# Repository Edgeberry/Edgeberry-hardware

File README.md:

The **Edgeberry Base Board** provides essential additional functionality for deploying the Raspberry Pi Model B as an IoT edge device in a real-world environment.

- **12 to 24VDC input power supply** for reliably powering the device with up to 3A at 5V.
- **Indicators and button** for providing status feedback and device interaction
- **Expansion slot** for Edgeberry Hardware Cartridges
- **Robust enclosure** for withstanding the environmental challenges of the real world
<br/>
<br clear="right"/>

## Edgeberry Device Software
For using your Edgeberry hardware with the Edgeberry ecosystem (e.g. the Edgeberry Dashboard), you'll need to install the [Edgeberry Device Software](https://github.com/Edgeberry/Edgeberry/). Follow [these installation steps](https://github.com/Edgeberry/Edgeberry?tab=readme-ov-file#installation). If you have different plans with this board, this software is not required for correct operation of any of its hardware components.

## (re)Writing the EEPROM
>[!important]
>**When you purchased the Edgeberry Hardware, the manufacturer has written the EEPROM**. If you are the manufacturer, or you're hacking your Edgeberry board, then continue with the following steps.

1) Close the `write protection` jumper (JP1) on the Edgeberry Hardware to enable writing the EEPROM
2) Download and build the [Raspberry Pi Hat eeprom utils](https://github.com/raspberrypi/hats) on your device 
3) Make the EEPROM file from the eeprom_settings.txt using `eepmake` <br> e.g. `$ ./eepmake eeprom_settings.txt edgeberry.eep`
4) Flash the EEPROM using `eepflash.sh` <br> e.g. `$ sudo ./eepflash -w -t=24c256 -f=edgeberry.eep`
5) Now `reboot` the device and check the device tree for your hat's settings <br> e.g. `$ cat /proc/device-tree/hat/vendor`)

## License & Collaboration
**Copyright© 2024 Sanne 'SpuQ' Santens**. This project is released under the [**CERN OHL-W**](./LICENSE.txt) license. The [Rules & Guidelines](https://github.com/Edgeberry/.github/blob/main/brand/Edgeberry_Trademark_Rules_and_Guidelines.md) apply to the usage of the Edgeberry™ brand.

### Collaboration

If you'd like to contribute to this project, please follow these guidelines:
1. Fork the repository and create your branch from `main`.
2. Make your changes and ensure they adhere to the project's design style and conventions.
3. Test your changes thoroughly.
4. Ensure your commits are descriptive and well-documented.
5. Open a pull request, describing the changes you've made and the problem or feature they address.

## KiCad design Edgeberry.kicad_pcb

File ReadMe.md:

# EDGEBERRY Hardware

The Raspberry Pi compatible 'hat' for the Edgeberry project.

## License and contribution
Copyright Sanne 'SpuQ' Santens. All rights reserved. For now.

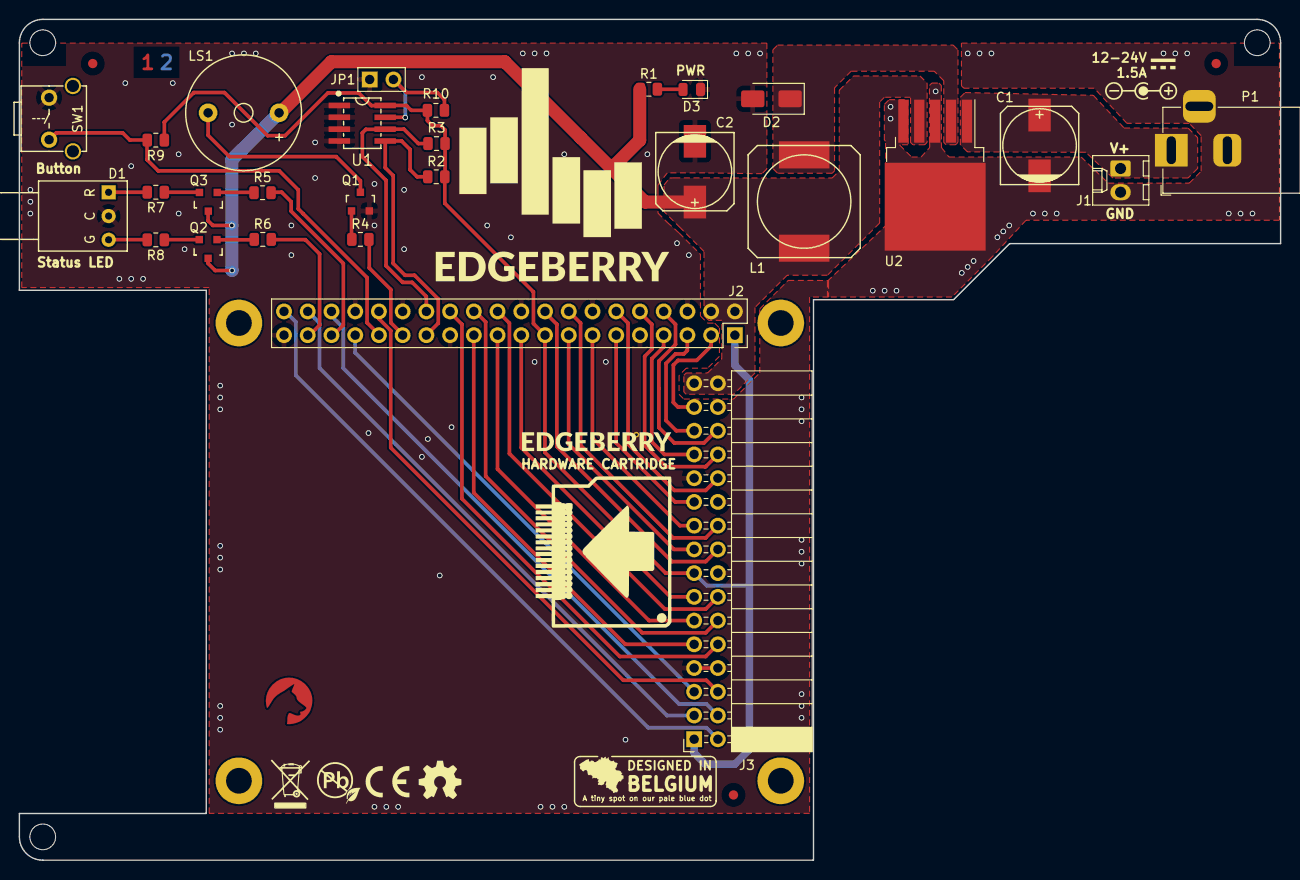
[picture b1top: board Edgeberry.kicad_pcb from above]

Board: 2 copper layers, 135.0 x 90.0 mm, 28 parts (0 on the bottom side), 43 nets.

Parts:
C1, C2: 330uF; c_elec_8x10
D1: Led_x2; bicolor_LED_right_angle
D2: SS54; D_SMA
D3: LED; LED_0805_2012Metric
J1: Molex_KK_1x02_P2.54mm; Molex_KK-254_AE-6410-02A_1x02_P2.54mm_Vertical
J2: Raspberry_Pi_2_3; PinSocket_2x20_P2.54mm_Vertical
J3: Edgeberry Cartridge Connector; PinSocket_2x16_P2.54mm_Horizontal
JP1: Jumper_2_Open; PinHeader_1x02_P2.54mm_Vertical
L1: 33uH; SELF-WE-PD-XXL
LS1: Buzzer; Buzzer_12x9.5RM7.6
P1: 12Vin; BarrelJack_Horizontal
Q1, Q2, Q3: BC547; SOT-23
R1, R7, R8: 270R; R_0805_2012Metric
R2, R3, R9, R10: 10k; R_0805_2012Metric
R4, R5, R6: 3k3; R_0805_2012Metric
SW1: SW_PUSH; tactile_switch_vertical
U1: 24LC256; SOIC_8
U2: LM2596S-5.0; TO-263-5_TabPin3

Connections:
+3V3: J2.1 (3V3), J2.17 (3V3), J3.1 (3V3_Power), J3.15 (3V3_Power), R2.1, R3.1, R9.1, R10.1, U1.8 (Vcc)
+5V: C2.1, J2.2 (5V), J2.4 (5V), J3.31 (5V_Power), J3.32 (5V_Power), L1.2, LS1.1, Q2.3 (C), Q3.3 (C), R1.1, U2.4 (FB)
+12V: C1.1, J1.1, P1.1, U2.1 (Vin)
GND: C1.2, C2.2, D1.2 (K), D2.2 (A), D3.1 (K), J1.2, J2.6 (GND), J2.9 (GND), J2.14 (GND), J2.20 (GND), J2.25 (GND), J2.30 (GND), J2.34 (GND), J2.39 (GND), J3.7 (GND), J3.8 (GND), J3.16 (GND), J3.22 (GND), J3.23 (GND), J3.30 (GND), JP1.1 (A), P1.2, P1.3, Q1.2 (E), SW1.1, U1.1 (A0), U1.2 (A1), U1.3 (A2), U1.4 (Vss), U2.3 (GND), U2.5 (on/off)
GPIO_4: J2.7 (GCLK0/GPIO4), J3.25 (GPIO_4)
GPIO_12: J2.32 (PWM0/GPIO12), J3.6 (GPIO_12)
GPIO_13: J2.33 (PWM1/GPIO13), J3.5 (GPIO_13)
GPIO_16: J2.36 (GPIO16), J3.4 (GPIO_16)
GPIO_17: J2.11 (GPIO17), J3.21 (GPIO_17)
GPIO_18: J2.12 (GPIO18/PWM0), J3.24 (GPIO_18)
GPIO_20: J2.38 (GPIO20/MOSI1), J3.3 (GPIO_20)
GPIO_21: J2.40 (GPIO21/SCLK1), J3.2 (GPIO_21)
GPIO_22: J2.15 (GPIO22), J3.17 (GPIO_22)
GPIO_23: J2.16 (GPIO23), J3.20 (GPIO_23)
GPIO_24: J2.18 (GPIO24), J3.18 (GPIO_24)
GPIO_25: J2.22 (GPIO25), J3.14 (GPIO_25)
GPIO_27: J2.13 (GPIO27), J3.19 (GPIO_27)
I2C_SCL: J2.5 (SCL/GPIO3), J3.27 (I2C_SCL)
I2C_SDA: J2.3 (SDA/GPIO2), J3.29 (I2C_SDA)
ID_SCL: J2.28 (ID_SC/GPIO1), R3.2, U1.6 (SCL)
ID_SDA: J2.27 (ID_SD/GPIO0), R2.2, U1.5 (SDA)
LED_green: J2.37 (GPIO26), R6.2
LED_red: J2.35 (GPIO19/MISO1), R5.2
unnamed: D1.1 (A1), R7.2
unnamed: D1.3 (A2), R8.2
unnamed: D2.1 (K), L1.1, U2.2 (Vout)
unnamed: D3.2 (A), R1.2
unnamed: Q1.1 (B), R4.1
unnamed: LS1.2, Q1.3 (C)
unnamed: Q2.1 (B), R6.1
unnamed: Q2.2 (E), R8.1
unnamed: Q3.1 (B), R5.1
unnamed: Q3.2 (E), R7.1
SPI_CS0: J2.24 (~CE0/GPIO8), J3.12 (SPI_CS0)
SPI_CS1: J2.26 (~CE1/GPIO7), J3.10 (SPI_CS1)
SPI_MISO: J2.21 (MISO0/GPIO9), J3.11 (SPI_MISO)
SPI_MOSI: J2.19 (MOSI0/GPIO10), J3.13 (SPI_MOSI)
SPI_SCLK: J2.23 (SCLK0/GPIO11), J3.9 (SPI_SCLK)
UART_RX: J2.10 (GPIO15/RXD), J3.26 (UART_Rx)
UART_TX: J2.8 (GPIO14/TXD), J3.28 (UART_Tx)
WP: JP1.2 (B), R10.2, U1.7 (WP)
btn_1: J2.31 (GCLK2/GPIO6), R9.2, SW1.2
buzzer: J2.29 (GCLK1/GPIO5), R4.2

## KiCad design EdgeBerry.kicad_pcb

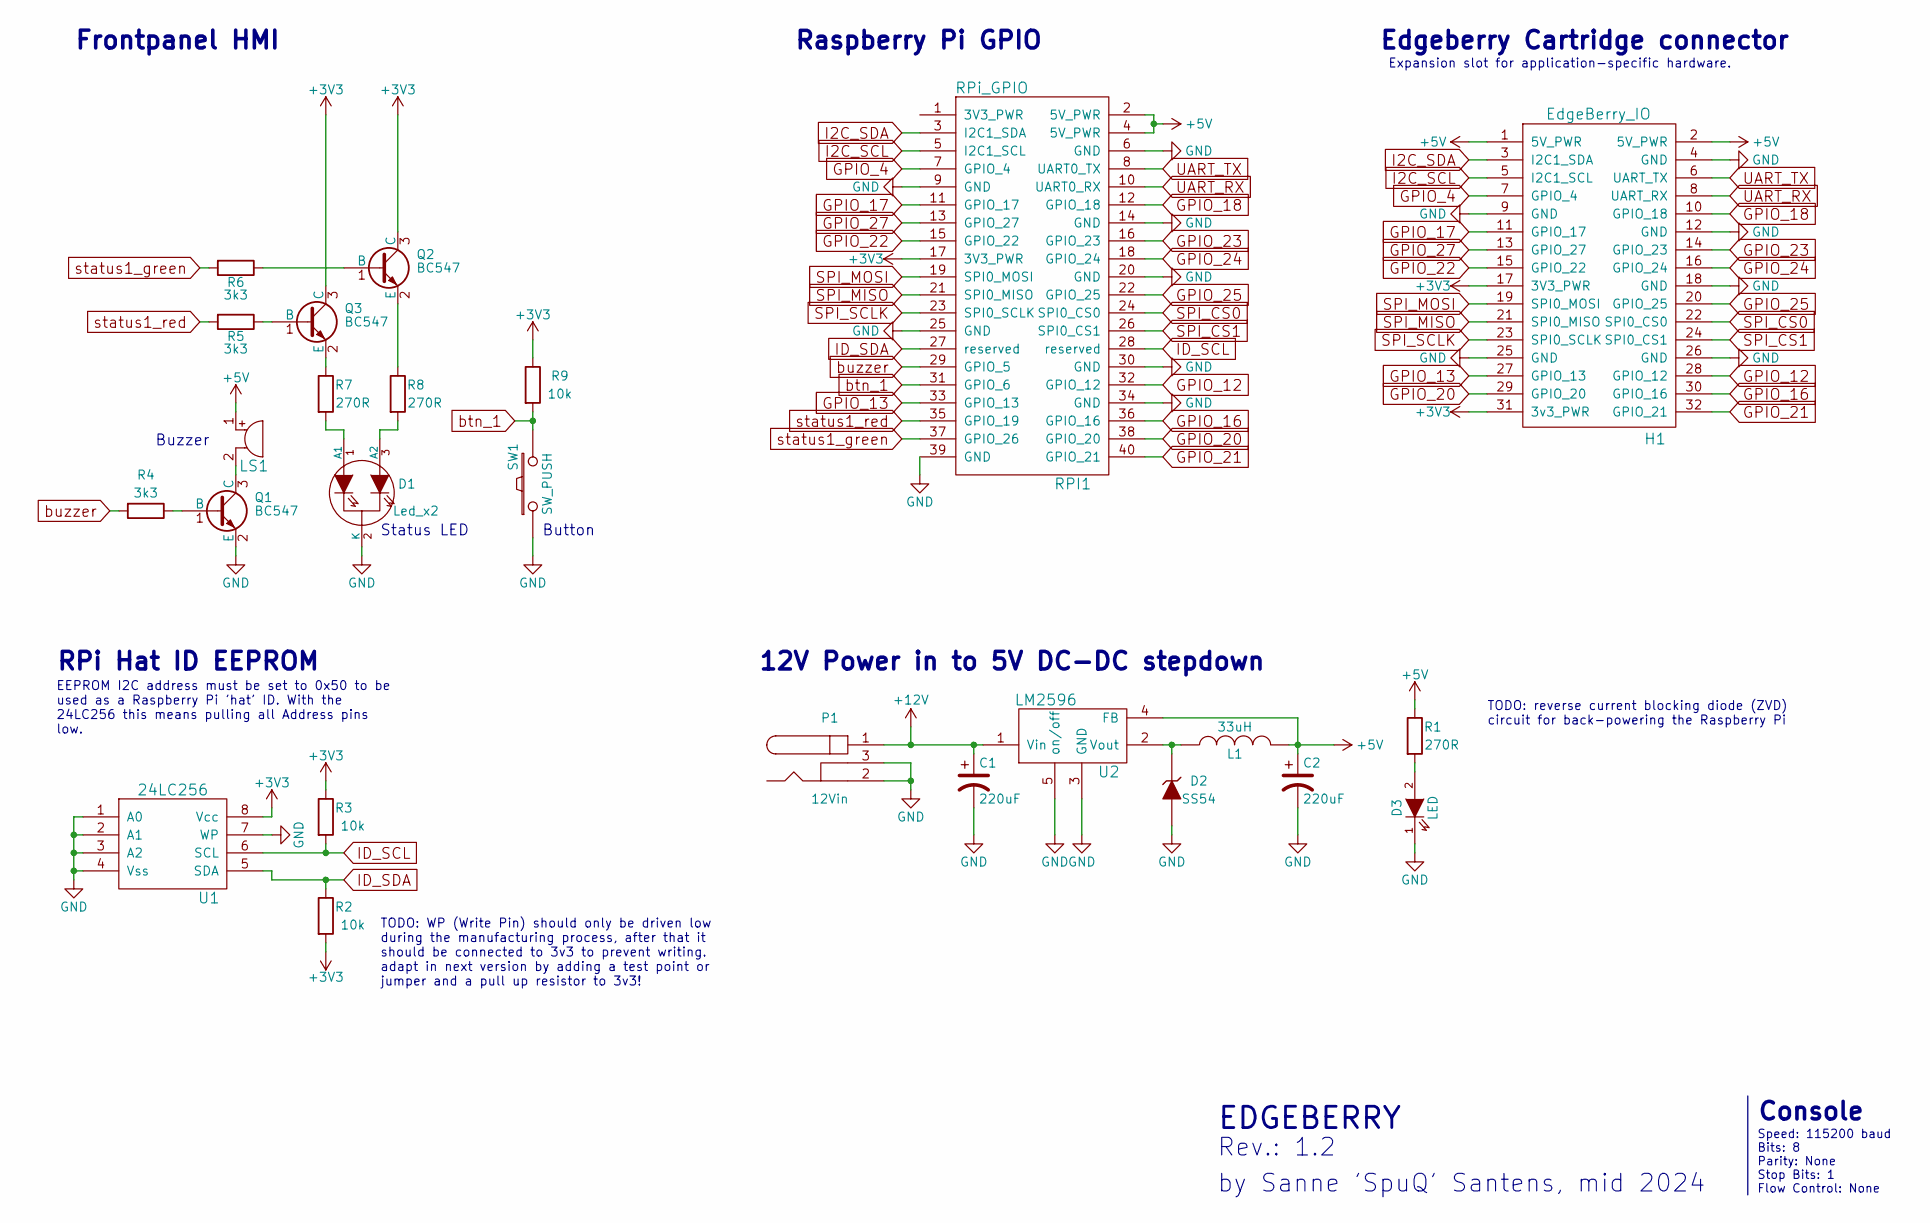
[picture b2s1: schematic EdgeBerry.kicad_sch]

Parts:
C1, C2: 220uF; c_elec_8x10
D1: Led_x2; bicolor_LED_right_angle
D2: SS54; SS54_Schottky_40V_5A
D3: LED; LED_0805_2012Metric
H1: EdgeBerry_IO
L1: 33uH; SELF-WE-PD-XXL
LS1: Buzzer; Buzzer_12x9.5RM7.6
P1: 12Vin; BarrelJack_Horizontal
Q1, Q2, Q3: BC547; SOT-23
R1, R7, R8: 270R; R_0805_2012Metric
R2, R3, R9: 10k; R_0805_2012Metric
R4, R5, R6: 3k3; R_0805_2012Metric
RPI1: RPi_GPIO; RPI_GPIO
SW1: SW_PUSH; tactile_switch_vertical
U1: 24LC256; SOIC_8
U2: LM2596; TO-263-5_TabPin3

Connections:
+3V3: H1.17 (3V3_PWR), H1.31 (3v3_PWR), Q2.3 (C), Q3.3 (C), R2.2, R3.1, R9.1, RPI1.17 (3V3_PWR), U1.8 (Vcc)
+5V: C2.1, H1.1 (5V_PWR), H1.2 (5V_PWR), L1.2, LS1.1, R1.1, RPI1.2 (5V_PWR), RPI1.4 (5V_PWR), U2.4 (FB)
+12V: C1.1, P1.1, U2.1 (Vin)
GND: C1.2, C2.2, D1.2 (K), D2.2 (A), D3.1 (K), H1.4 (GND), H1.9 (GND), H1.12 (GND), H1.18 (GND), H1.25 (GND), H1.26 (GND), P1.2, P1.3, Q1.2 (E), RPI1.6 (GND), RPI1.9 (GND), RPI1.14 (GND), RPI1.20 (GND), RPI1.25 (GND), RPI1.30 (GND), RPI1.34 (GND), RPI1.39 (GND), SW1.1, U1.1 (A0), U1.2 (A1), U1.3 (A2), U1.4 (Vss), U1.7 (WP), U2.3 (GND), U2.5 (on/off)
GPIO_4: H1.7 (GPIO_4), RPI1.7 (GPIO_4)
GPIO_12: H1.28 (GPIO_12), RPI1.32 (GPIO_12)
GPIO_13: H1.27 (GPIO_13), RPI1.33 (GPIO_13)
GPIO_16: H1.30 (GPIO_16), RPI1.36 (GPIO_16)
GPIO_17: H1.11 (GPIO_17), RPI1.11 (GPIO_17)
GPIO_18: H1.10 (GPIO_18), RPI1.12 (GPIO_18)
GPIO_20: H1.29 (GPIO_20), RPI1.38 (GPIO_20)
GPIO_21: H1.32 (GPIO_21), RPI1.40 (GPIO_21)
GPIO_22: H1.15 (GPIO_22), RPI1.15 (GPIO_22)
GPIO_23: H1.14 (GPIO_23), RPI1.16 (GPIO_23)
GPIO_24: H1.16 (GPIO_24), RPI1.18 (GPIO_24)
GPIO_25: H1.20 (GPIO_25), RPI1.22 (GPIO_25)
GPIO_27: H1.13 (GPIO_27), RPI1.13 (GPIO_27)
I2C_SCL: H1.5 (I2C1_SCL), RPI1.5 (I2C1_SCL)
I2C_SDA: H1.3 (I2C1_SDA), RPI1.3 (I2C1_SDA)
ID_SCL: R3.2, RPI1.28 (reserved), U1.6 (SCL)
ID_SDA: R2.1, RPI1.27 (reserved), U1.5 (SDA)
unnamed: D1.1 (A1), R7.2
unnamed: D1.3 (A2), R8.2
unnamed: D2.1 (K), L1.1, U2.2 (Vout)
unnamed: D3.2 (A), R1.2
unnamed: LS1.2, Q1.3 (C)
unnamed: Q1.1 (B), R4.1
unnamed: Q2.1 (B), R6.1
unnamed: Q2.2 (E), R8.1
unnamed: Q3.1 (B), R5.1
unnamed: Q3.2 (E), R7.1
SPI_CS0: H1.22 (SPI0_CS0), RPI1.24 (SPI0_CS0)
SPI_CS1: H1.24 (SPI0_CS1), RPI1.26 (SPI0_CS1)
SPI_MISO: H1.21 (SPI0_MISO), RPI1.21 (SPI0_MISO)
SPI_MOSI: H1.19 (SPI0_MOSI), RPI1.19 (SPI0_MOSI)
SPI_SCLK: H1.23 (SPI0_SCLK), RPI1.23 (SPI0_SCLK)
UART_RX: H1.8 (UART_RX), RPI1.10 (UART0_RX)
UART_TX: H1.6 (UART_TX), RPI1.8 (UART0_TX)
btn_1: R9.2, RPI1.31 (GPIO_6), SW1.2
buzzer: R4.2, RPI1.29 (GPIO_5)
status1_green: R6.2, RPI1.37 (GPIO_26)
status1_red: R5.2, RPI1.35 (GPIO_19)

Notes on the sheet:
Button
Speed: 115200 baud Bits: 8 Parity: None Stop Bits: 1 Flow Control: None
by Sanne 'SpuQ' Santens, mid 2024
EEPROM I2C address must be set to 0x50 to be used as a Raspberry Pi 'hat' ID. With the 24LC256 this means pulling all Address pins low.
Frontpanel HMI
12V Power in to 5V DC-DC stepdown
Raspberry Pi GPIO
TODO: reverse current blocking diode (ZVD) circuit for back-powering the Raspberry Pi
RPi Hat ID EEPROM
Console
Rev.: 1.2
Buzzer
Status LED
TODO: WP (Write Pin) should only be driven low during the manufacturing process, after that it should be connected to 3v3 to prevent writing. adapt in next version by adding a test point or jumper and a pull up resistor to 3v3!
EDGEBERRY
Expansion slot for application-specific hardware.
Edgeberry Cartridge connector

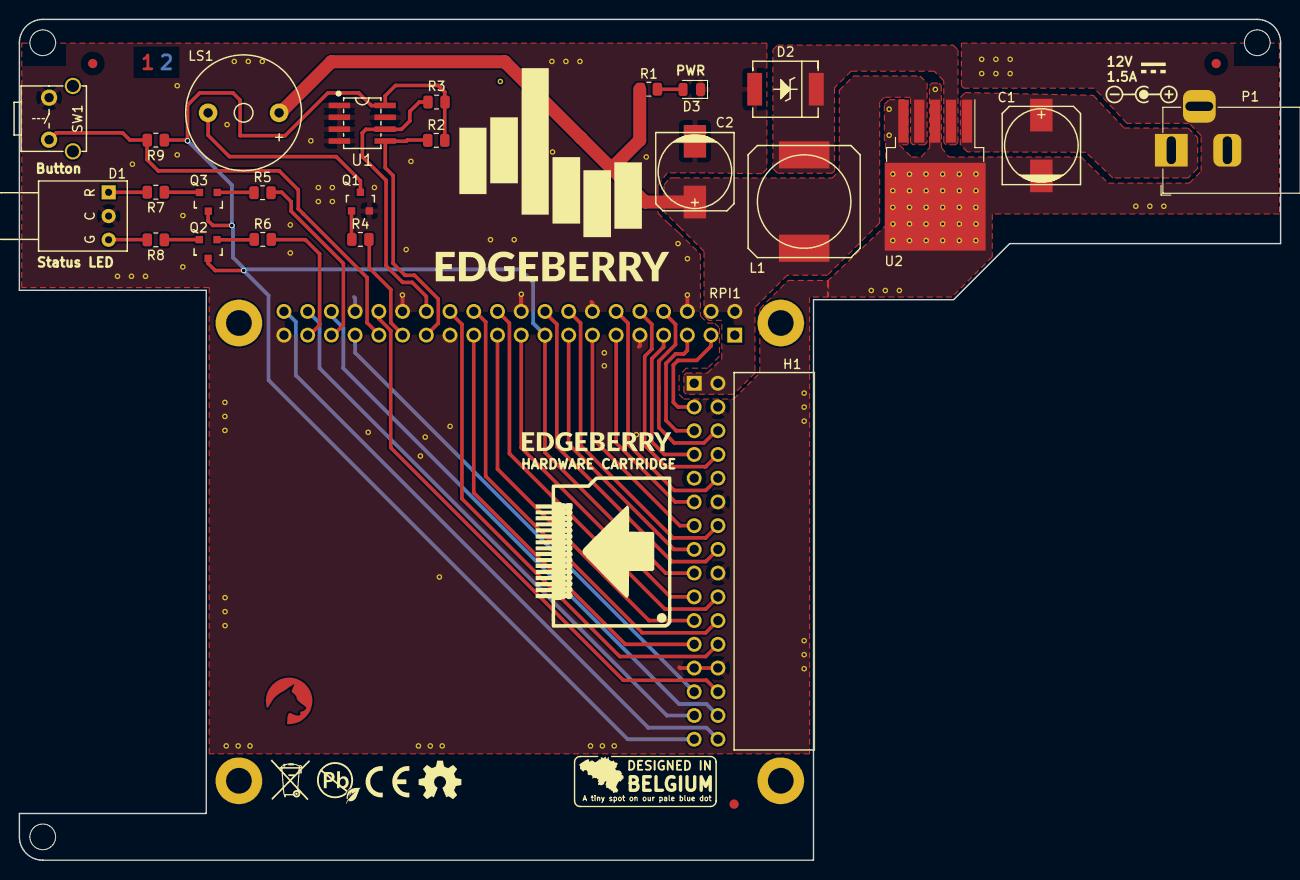
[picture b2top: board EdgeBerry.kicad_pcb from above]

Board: 2 copper layers, 135.0 x 90.0 mm, 25 parts (1 on the bottom side), 42 nets.

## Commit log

2024-05-14 Edgeberry v1.2 on GitHub
2024-05-14 ReadMe: initialization
2024-05-14 ReadMe was renamed
2024-05-15 Schematic: in-schematic todo's moved to GitHub issues
2024-05-15 Schematic: cleanup + increased readability
2024-05-15 Update file naming
2024-05-15 ReadMe: assembly instructions
2024-05-15 ReadMe: styling improvements
2024-05-15 ReadMe: no more Lorem ipsum
2024-05-15 ReadMe: banner update + Device assembly text
2024-05-15 ReadMe: Edgeberry Software installation + collaboration
2024-05-15 ReadMe: some corrections
2024-05-16 Buck convertor capacitors updated to 330uF
2024-05-16 EEPROM write protection circuit + update version to 1.3
2024-05-16 ReadMe: update rendering to V1.3
2024-05-16 ReadMe: introduction text improvement, with links
2024-05-16 ReadMe: introduction text improvement
2024-05-16 Board: aesthetic improvements
2024-05-16 Status LED on 5V instead of 3V3 + silkscreen aesthetics
2024-05-16 ReadMe: writing the EEPROM
2024-05-16 ReadMe: writing the EEPROM - all steps
2024-05-16 ReadMe: writing the EEPROM cleanup
2024-05-16 Board: last pre-manufacturing adaptations
2024-05-17 Added a Molex 2Pin header on 12V
2024-05-17 Board: improvements for fabrications
2024-05-17 Board: improvements for fabrications + assembly guide
2024-05-17 EEPROM: hardware version 1.4
2024-05-18 Bugfix RPi footprint + via's are via's now instead footprints. KiCad * update.
2024-05-19 cleanup + documentation
2024-05-19 Open Source Hardware license: CERN-OHL-W
2024-05-21 ReadMe: rendering 1.5 design
2024-05-21 ReadMe: Logo use restriction warning
2024-05-21 ReadMe: Logo use restriction warning - typo's
2024-05-21 ReadMe: Edgeberry Project explaination
2024-05-22 Buck convertor: Schottky diode footprint modification
2024-05-22 ReadMe: migrate project info to organization ReadMe
2024-05-29 Bugfix: R7 and R8 lower resistors as temp fix
2024-06-25 ReadMe: added link to trademark rules & guidelines
2024-06-25 ReadMe: critical typo in EEPROM guides
2024-06-25 ReadMe: Device software guide
2024-06-25 ReadMe: cleanup
2024-08-25 ReadMe: Tindie button
2024-08-30 Edgeberry enclosure FreeCAD design
2024-08-31 Documentation: Enclosure Mechanical Drawing
2024-12-07 Edgeberry rev1.7
2024-12-07 removing old files
2024-12-07 Enclosure
2024-12-08 Enclosure: Raspberry Pi 3B/3B+/5B faceplate improvement
2024-12-08 Cleanup
2024-12-08 EEPROM: Hardware rev 1.7
2024-12-08 Update gitignore to prevent garbage in repo
2024-12-08 Enclosure: optimizations for Rev. 1.7
2024-12-12 Enclosure: Mechanical drawing update
2024-12-22 ReadMe: Remove Tindie link
2024-12-22 ReadMe: removed assembly info
2025-02-15 Cleanup: enclosure

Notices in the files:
Edgeberry.kicad_pcb:
Copyright© 2024 Sanne 'SpuQ' Santens. This design is released under
the CERN OHL-W license on GitHub.
